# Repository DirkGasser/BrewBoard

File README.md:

# BrewBoard
Kicad Definition of the BrewBoard, the board which is connected to the raspberry pi and control the home brew factory

Board is designed with three wire bridges, so that a single sided board is sufficient. That way the board can be built home made.

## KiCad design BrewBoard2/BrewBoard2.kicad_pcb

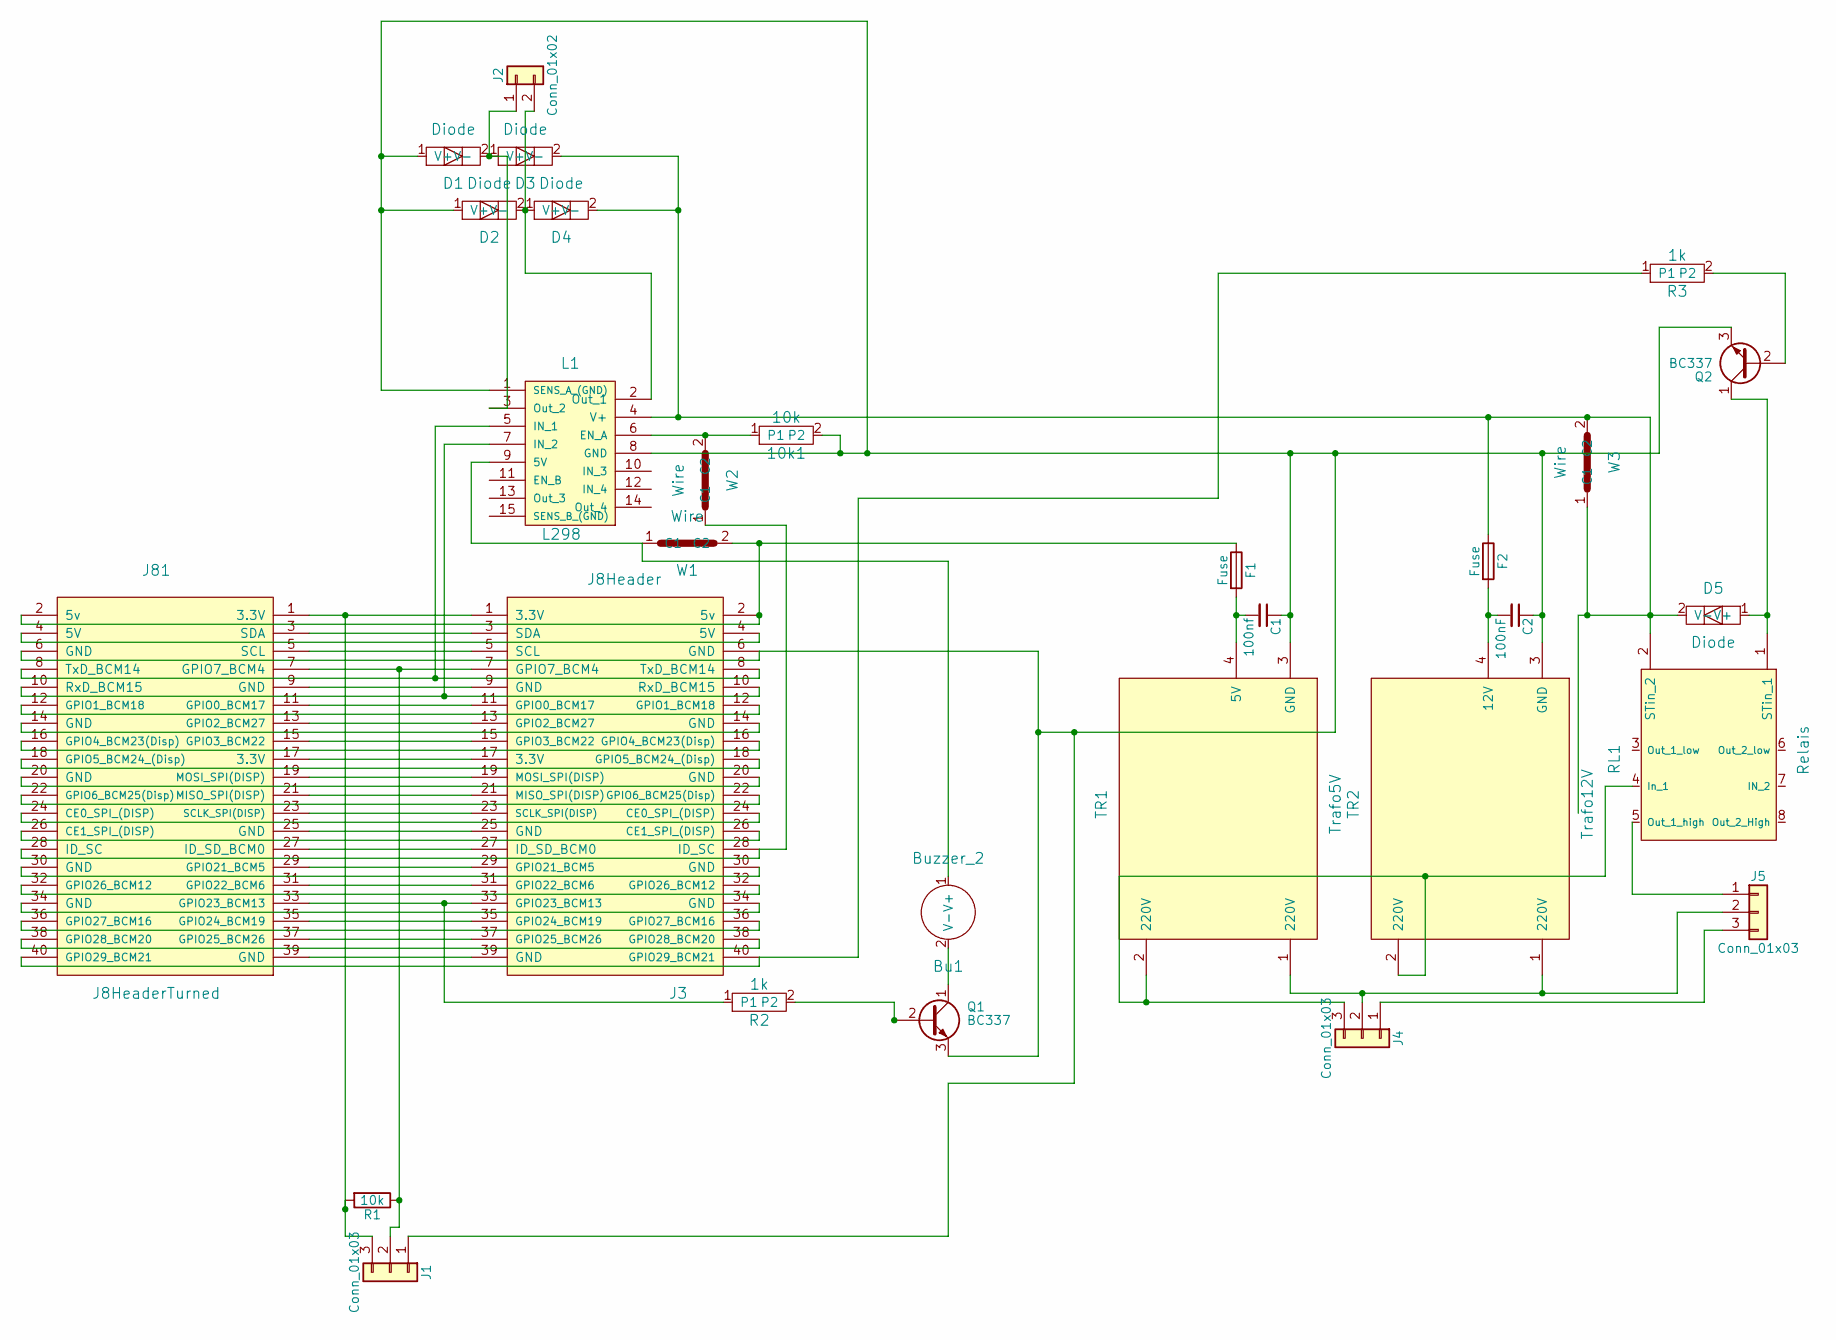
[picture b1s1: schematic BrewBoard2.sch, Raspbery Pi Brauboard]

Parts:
10k1: 10k; Resistor
Bu1: Buzzer_2; Buzzer1x2
C1: 100nf; Capacitor_Small
C2: 100nF; Capacitor_Small
D1, D2, D3, D4, D5: Diode
F1, F2: Fuse
J1: Conn_01x03; Conn_Small1x3
J2: Conn_01x02; Conn_Small1x2
J3: J8Header; RaspiConnector
J4, J5: Conn_01x03; Connector1x3
J81: J8HeaderTurned; RaspiConnectorTurned
L1: L298
Q1, Q2: BC337
R1: 10k; Resistor
R2, R3: 1k; Resistor
RL1: Relais
TR1: Trafo5V; Trafo
TR2: Trafo12V; Trafo
W1: Wire; Wire_long
W2, W3: Wire; Wire_Short

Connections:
unnamed: 10k1.1, L1.6 (EN_A), W2.2 (C2)
unnamed: 10k1.2, C1.1, C2.1, D1.1 (V+), D2.1 (V+), J1.1, J3.6 (GND), J81.6 (GND), L1.1 (SENS_A_(GND)), L1.8 (GND), Q1.3 (E), Q2.3 (E), TR1.3 (GND), TR2.3 (GND)
unnamed: Bu1.1 (V+), L1.9 (5V), W1.1 (C1)
unnamed: Bu1.2 (V-), Q1.1 (C)
unnamed: C1.2, F1.2, TR1.4 (5V)
unnamed: C2.2, F2.2, TR2.4 (12V)
unnamed: D1.2 (V-), D3.1 (V+), J2.1, L1.3 (Out_2)
unnamed: D2.2 (V-), D4.1 (V+), J2.2, L1.2 (Out_1)
unnamed: D3.2 (V-), D4.2 (V-), D5.2 (V-), F2.1, L1.4 (V+), RL1.2 (STin_2), W3.1 (C1), W3.2 (C2)
unnamed: D5.1 (V+), Q2.1 (C), RL1.1 (STin_1)
unnamed: F1.1, J3.2 (5v), J81.2 (5v), W1.2 (C2)
unnamed: J1.2, J3.7 (GPIO7_BCM4), J81.7 (GPIO7_BCM4), R1.1
unnamed: J1.3, J3.1 (3.3V), J81.1 (3.3V), R1.2
unnamed: J3.3 (SDA), J81.3 (SDA)
unnamed: J3.4 (5V), J81.4 (5V)
unnamed: J3.5 (SCL), J81.5 (SCL)
unnamed: J3.8 (TxD_BCM14), J81.8 (TxD_BCM14), L1.5 (IN_1)
unnamed: J3.9 (GND), J81.9 (GND)
unnamed: J3.10 (RxD_BCM15), J81.10 (RxD_BCM15), L1.7 (IN_2)
unnamed: J3.11 (GPIO0_BCM17), J81.11 (GPIO0_BCM17)
unnamed: J3.12 (GPIO1_BCM18), J81.12 (GPIO1_BCM18)
unnamed: J3.13 (GPIO2_BCM27), J81.13 (GPIO2_BCM27)
unnamed: J3.14 (GND), J81.14 (GND)
unnamed: J3.15 (GPIO3_BCM22), J81.15 (GPIO3_BCM22)
unnamed: J3.16 (GPIO4_BCM23(Disp)), J81.16 (GPIO4_BCM23(Disp))
unnamed: J3.17 (3.3V), J81.17 (3.3V)
unnamed: J3.18 (GPIO5_BCM24_(Disp)), J81.18 (GPIO5_BCM24_(Disp))
unnamed: J3.19 (MOSI_SPI(DISP)), J81.19 (MOSI_SPI(DISP))
unnamed: J3.20 (GND), J81.20 (GND)
unnamed: J3.21 (MISO_SPI(DISP)), J81.21 (MISO_SPI(DISP))
unnamed: J3.22 (GPIO6_BCM25(Disp)), J81.22 (GPIO6_BCM25(Disp))
unnamed: J3.23 (SCLK_SPI(DISP)), J81.23 (SCLK_SPI(DISP))
unnamed: J3.24 (CE0_SPI_(DISP)), J81.24 (CE0_SPI_(DISP))
unnamed: J3.25 (GND), J81.25 (GND)
unnamed: J3.26 (CE1_SPI_(DISP)), J81.26 (CE1_SPI_(DISP))
unnamed: J3.27 (ID_SD_BCM0), J81.27 (ID_SD_BCM0)
unnamed: J3.28 (ID_SC), J81.28 (ID_SC), W2.1 (C1)
unnamed: J3.29 (GPIO21_BCM5), J81.29 (GPIO21_BCM5)
unnamed: J3.30 (GND), J81.30 (GND)
unnamed: J3.31 (GPIO22_BCM6), J81.31 (GPIO22_BCM6)
unnamed: J3.32 (GPIO26_BCM12), J81.32 (GPIO26_BCM12)
unnamed: J3.33 (GPIO23_BCM13), J81.33 (GPIO23_BCM13), R2.1
unnamed: J3.34 (GND), J81.34 (GND)
unnamed: J3.35 (GPIO24_BCM19), J81.35 (GPIO24_BCM19)
unnamed: J3.36 (GPIO27_BCM16), J81.36 (GPIO27_BCM16)
unnamed: J3.37 (GPIO25_BCM26), J81.37 (GPIO25_BCM26)
unnamed: J3.38 (GPIO28_BCM20), J81.38 (GPIO28_BCM20)
unnamed: J3.39 (GND), J81.39 (GND)
unnamed: J3.40 (GPIO29_BCM21), J81.40 (GPIO29_BCM21), R3.1
unnamed: J4.1, J5.3
unnamed: J4.2, J5.2, TR1.1 (220V), TR2.1 (220V)
unnamed: J4.3, RL1.4 (In_1), TR1.2 (220V), TR2.2 (220V)
unnamed: J5.1, RL1.5 (Out_1_high)
unnamed: Q1.2 (B), R2.2
unnamed: Q2.2 (B), R3.2

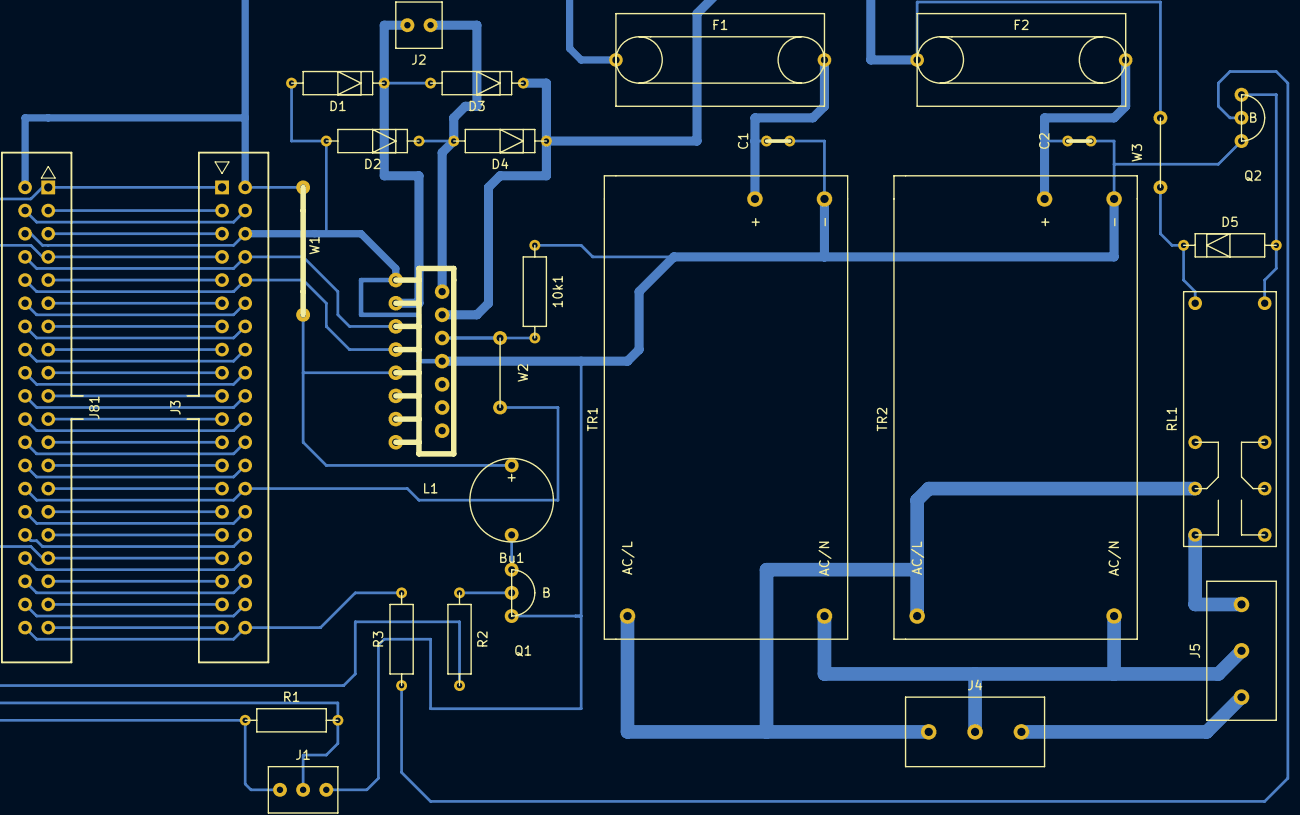
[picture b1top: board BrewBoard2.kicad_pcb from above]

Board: 2 copper layers, 29 parts (0 on the bottom side), 55 nets.

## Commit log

2018-10-08 Versiont 1
2018-10-24 Korrekturen
2018-10-26 Buzzer 5v
2018-11-11 second design with turned header
2018-11-17 First Final
